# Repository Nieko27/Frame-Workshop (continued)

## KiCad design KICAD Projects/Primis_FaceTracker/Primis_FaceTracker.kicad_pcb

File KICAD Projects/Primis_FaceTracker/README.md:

### Status

| 🛑R&D | hw: EV2 | 
| -------- | ------- |

> This accessory is experimental. The latest hardware revision is either untested, incomplete, or broken. Capabilities are unproven. Form factor and design requirements may change entirely. Intended for use by hardware contributors.

### TODO
* Copper pads under power supply
* Clean up and condense
* ESD Protection
# Face Tracker (Headset-Agnostic Version)
Headset-agnostic face tracker. Can be used with Frame by using the USB-C port on the battery.
## Current Isseus
Q1 is setup improperly, removing it and R10 as well as bridging the now empty pads solves the issue. Will fix in EV3 along with some changes to layout and LEDs.

### Schematics

### PCB

### EV2

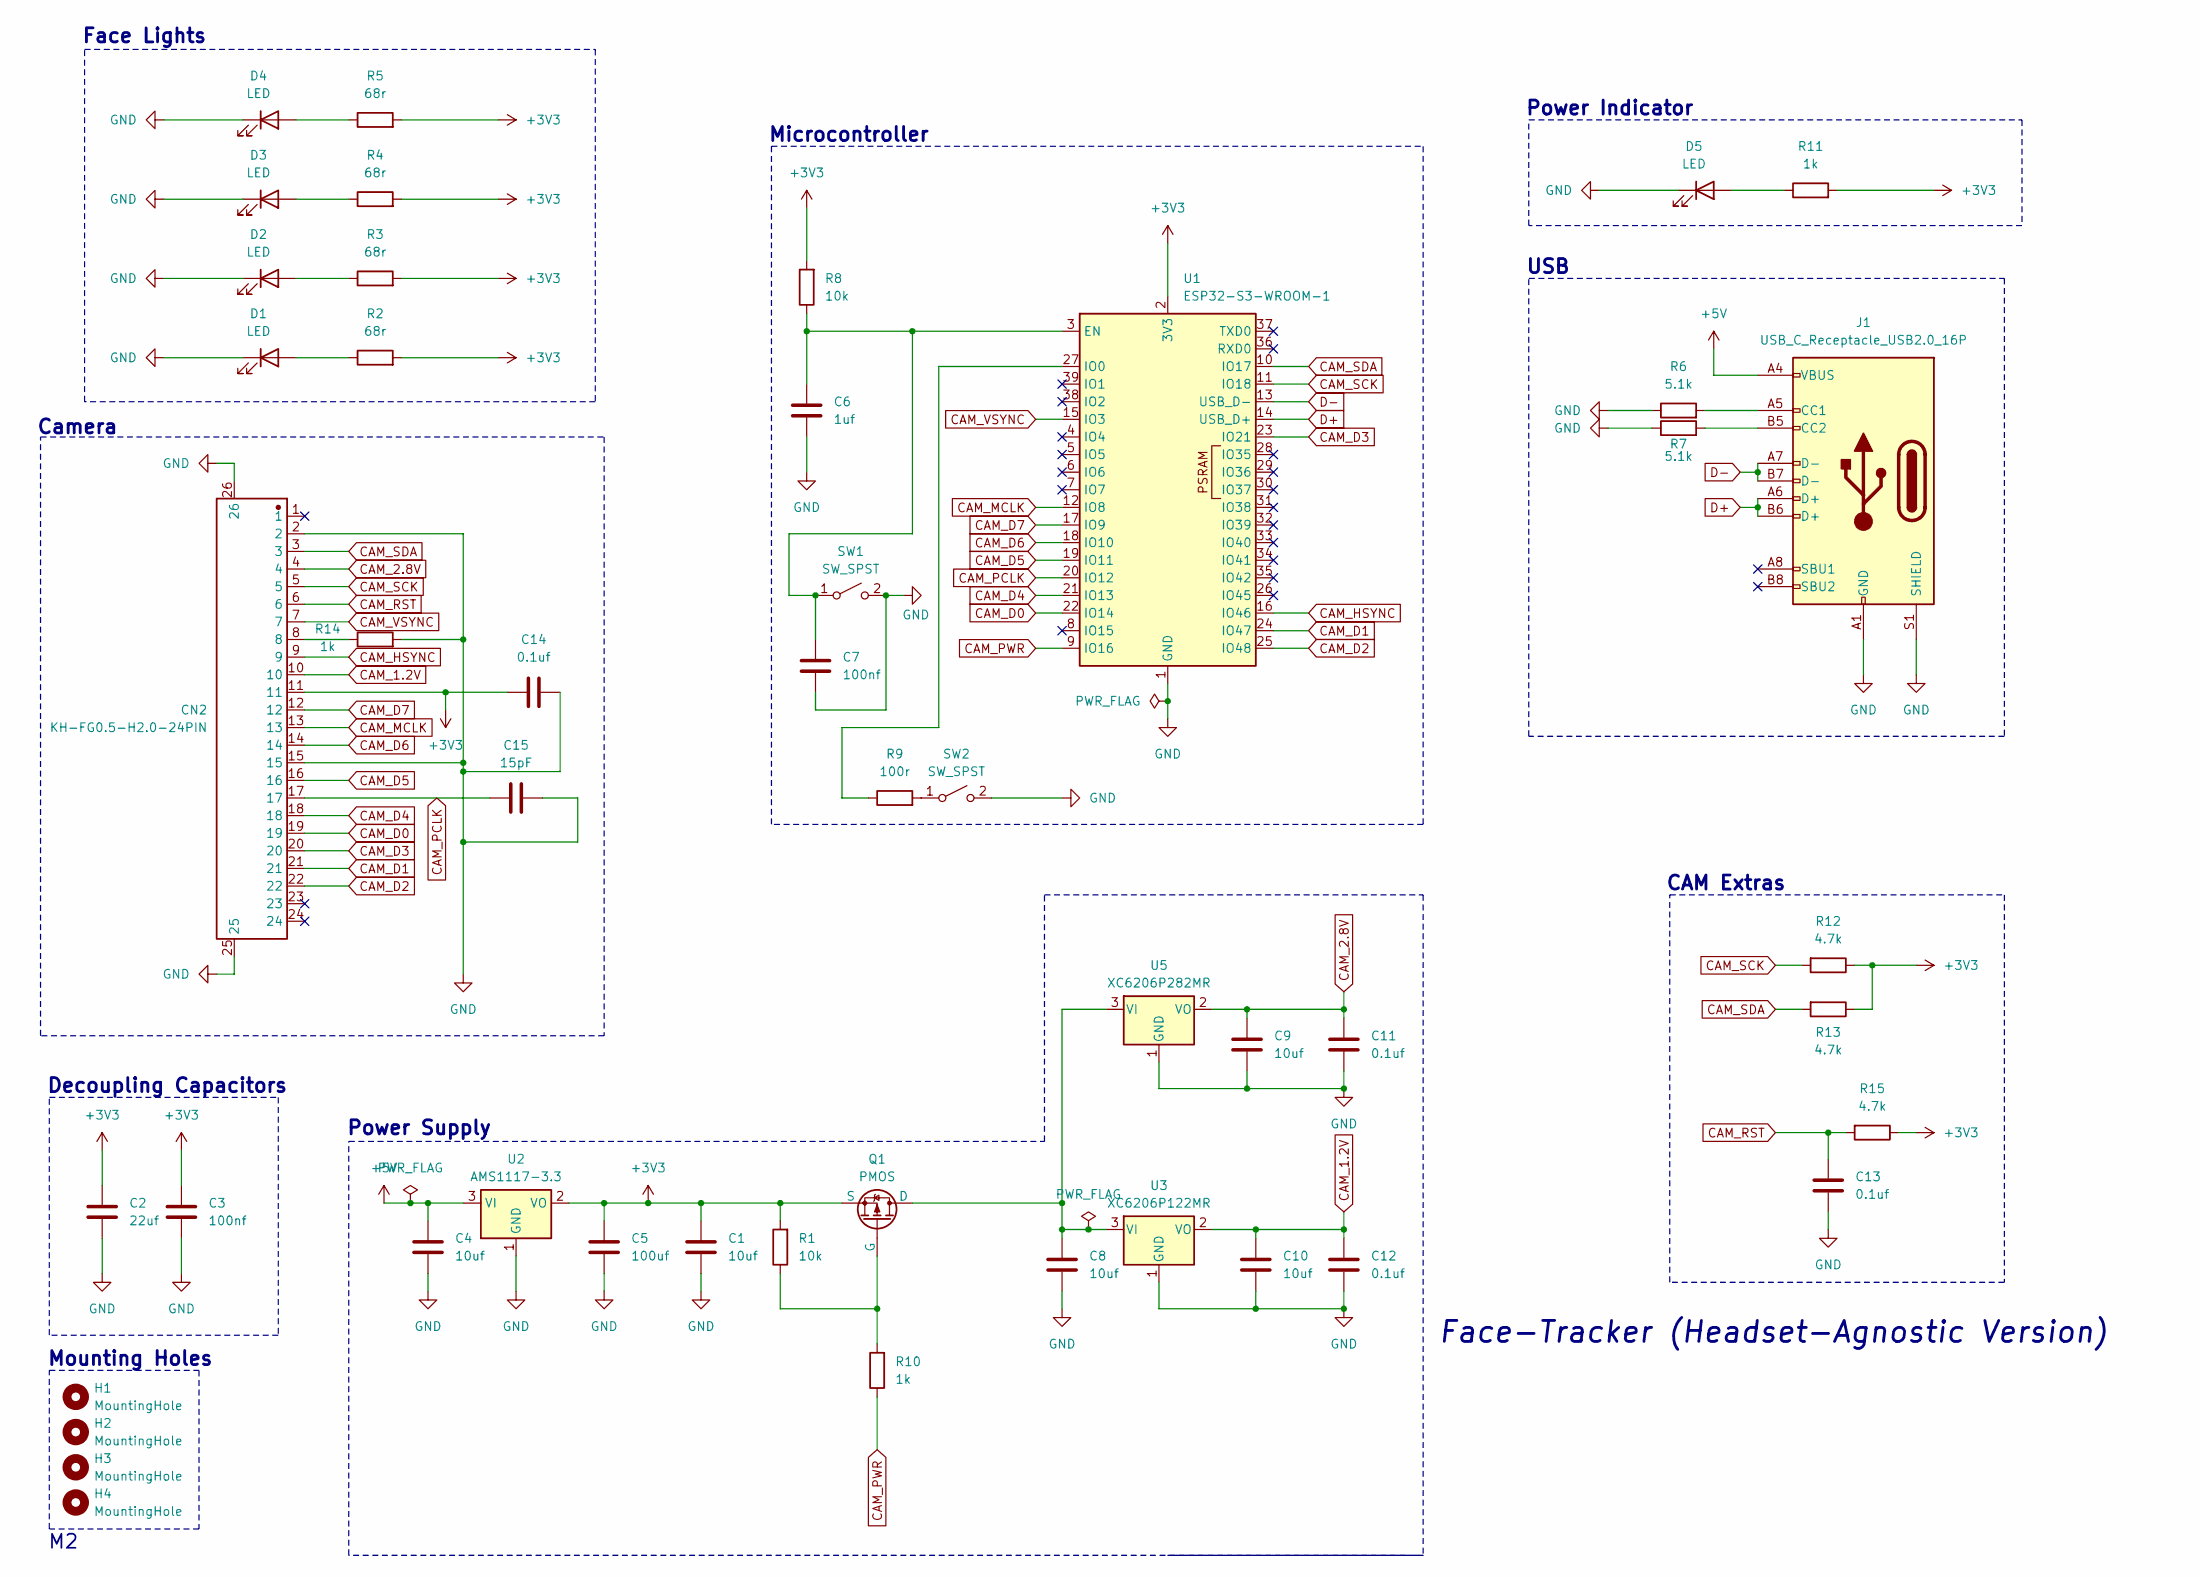
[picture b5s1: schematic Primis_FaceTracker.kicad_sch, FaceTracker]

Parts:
C1, C4, C8, C9, C10: 10uf; C_0805_2012Metric
C2: 22uf; C_0805_2012Metric
C3, C7: 100nf; C_0603_1608Metric
C5: 100uf; C_1206_3216Metric
C6: 1uf; C_0603_1608Metric
C11, C12, C13, C14: 0.1uf; C_0603_1608Metric
C15: 15pF; C_0603_1608Metric
CN2: KH-FG0.5-H2.0-24PIN; FPC-SMD_KH-FG0.5-H2.0-24PIN
D1, D2, D3, D4, D5: LED; LED_0805_2012Metric
H1, H2, H3, H4: MountingHole; MountingHole_2.2mm_M2
J1: USB_C_Receptacle_USB2.0_16P; USB_C_Receptacle_HRO_TYPE-C-31-M-12
Q1: PMOS; SOT-23
R1, R8: 10k; R_0805_2012Metric
R2, R3, R4, R5: 68r; R_0603_1608Metric
R6, R7: 5.1k; R_0805_2012Metric
R9: 100r; R_0603_1608Metric
R10, R11, R14: 1k; R_0805_2012Metric
R12, R13, R15: 4.7k; R_0805_2012Metric
SW1, SW2: SW_SPST; SW_SPST_TS-1088-xR020
U1: ESP32-S3-WROOM-1
U2: AMS1117-3.3; SOT-223-3_TabPin2
U3: XC6206P122MR; SOT-23-3
U5: XC6206P282MR; SOT-23-3

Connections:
+3V3: C1.1, C2.1, C3.1, C5.1, C14.1, CN2.11, Q1.3 (S), R1.2, R2.2, R3.2, R4.2, R5.2, R8.2, R11.2, R12.1, R13.1, R15.1, U1.2 (3V3), U2.2 (VO)
+5V: C4.1, J1.A4 (VBUS), J1.A9 (VBUS), J1.B4 (VBUS), J1.B9 (VBUS), U2.3 (VI)
CAM_1.2V: C10.1, C12.1, CN2.10, U3.2 (VO)
CAM_2.8V: C9.1, C11.1, CN2.4, U5.2 (VO)
CAM_D0: CN2.19, U1.22 (IO14)
CAM_D1: CN2.21, U1.24 (IO47)
CAM_D2: CN2.22, U1.25 (IO48)
CAM_D3: CN2.20, U1.23 (IO21)
CAM_D4: CN2.18, U1.21 (IO13)
CAM_D5: CN2.16, U1.19 (IO11)
CAM_D6: CN2.14, U1.18 (IO10)
CAM_D7: CN2.12, U1.17 (IO9)
CAM_HSYNC: CN2.9, U1.16 (IO46)
CAM_MCLK: CN2.13, U1.12 (IO8)
CAM_PCLK: C15.1, CN2.17, U1.20 (IO12)
CAM_PWR: R10.1, U1.9 (IO16)
CAM_RST: C13.1, CN2.6, R15.2
CAM_SCK: CN2.5, R12.2, U1.11 (IO18)
CAM_SDA: CN2.3, R13.2, U1.10 (IO17)
CAM_VSYNC: CN2.7, U1.15 (IO3)
D+: J1.A6 (D+), J1.B6 (D+), U1.14 (USB_D+)
D-: J1.A7 (D-), J1.B7 (D-), U1.13 (USB_D-)
GND: C1.2, C2.2, C3.2, C4.2, C5.2, C6.2, C7.1, C8.2, C9.2, C10.2, C11.2, C12.2, C13.2, C14.2, C15.2, CN2.2, CN2.15, CN2.25, CN2.26, D1.1 (K), D2.1 (K), D3.1 (K), D4.1 (K), D5.1 (K), J1.A1 (GND), J1.A12 (GND), J1.B1 (GND), J1.B12 (GND), J1.S1 (SHIELD), R6.1, R7.1, R14.2, SW1.2 (B), SW2.2 (B), U1.1 (GND), U1.40 (GND), U1.41 (GND), U2.1 (GND), U3.1 (GND), U5.1 (GND)
unnamed: CN2.8, R14.1
unnamed: D1.2 (A), R2.1
unnamed: D2.2 (A), R3.1
unnamed: D3.2 (A), R4.1
unnamed: D4.2 (A), R5.1
unnamed: D5.2 (A), R11.1
unnamed: J1.A5 (CC1), R6.2
unnamed: J1.B5 (CC2), R7.2
unnamed: C8.1, Q1.1 (D), U3.3 (VI), U5.3 (VI)
unnamed: Q1.2 (G), R1.1, R10.2
unnamed: C6.1, C7.2, R8.1, SW1.1 (A), U1.3 (EN)
unnamed: R9.2, SW2.1 (A)
unnamed: R9.1, U1.27 (IO0)

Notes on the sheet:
Decoupling Capacitors
Face Lights
Mounting Holes
Microcontroller
Power Indicator
Face-Tracker (Headset-Agnostic Version)
USB
Camera
CAM Extras
Power Supply

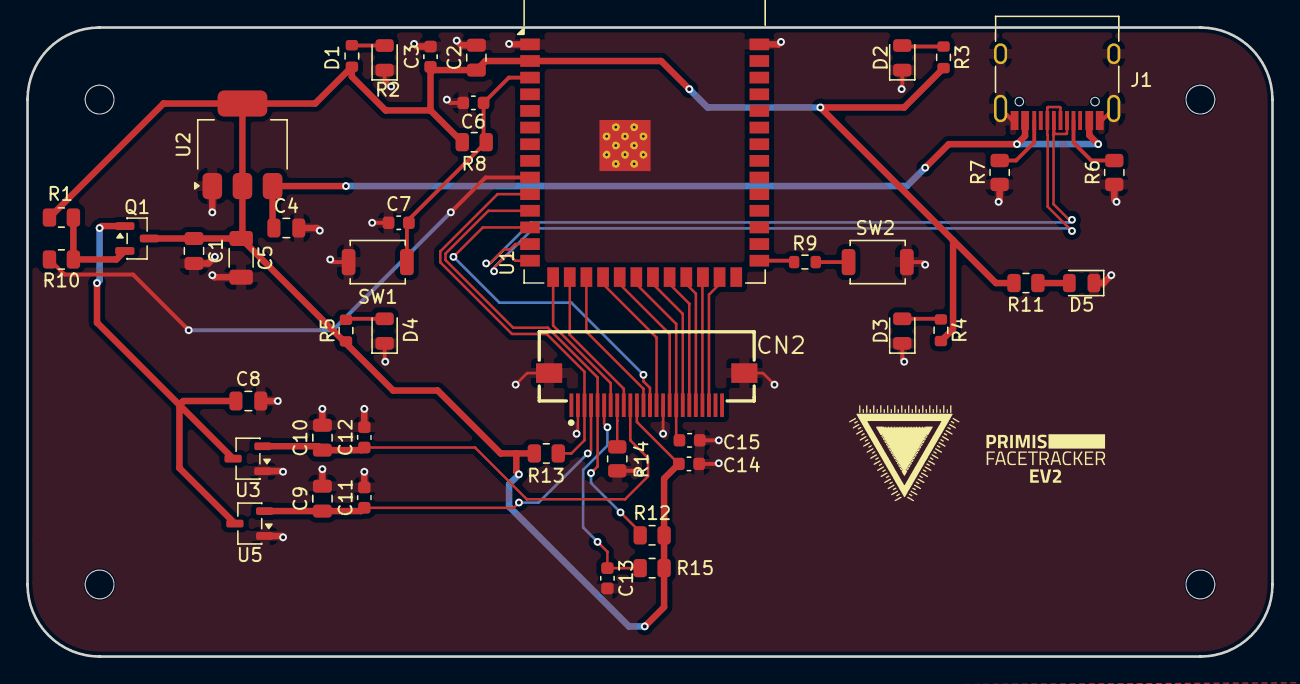
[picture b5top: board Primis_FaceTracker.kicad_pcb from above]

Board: 2 copper layers, 95.0 x 48.0 mm, 48 parts (0 on the bottom side), 36 nets.

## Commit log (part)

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2026-01-17 Clean
2026-01-17 Structure
2026-01-17 Structure2
2026-01-26 NameFix
2026-02-11 Face Tracker and Versipellis Clean
    -Organised the face tracker PCB a bit more
    -Added TODO to face tracker README
    -Organised Versipellis schematics
    -Updated images
2026-02-17 Gerbers plus clean up
    -Added gerbers for the face tracker and versipellis
    -Shrunk the face tracker and cleaned up
    -Fixed some DRC issues with both projects
2026-03-10 Quick Update
2026-04-26 FaceTracker fixes and Dongle rework
    -Fixed some mistakes on the Facetracker with the camera power lines.
    -Some part swaps and additions on the dongle to match the JLCPCBs catalogue
2026-04-27 Usb swap
    -Changed the dongle to another usb
2026-05-02 Dongle Cleanup
    -CLeanup before final
2026-05-02 Versipellis EV1 Final + General Github updates
    -Fixed a few remaining issues with Versipellis EV1
    -Created production files for Versipellis
    -Updated pictures for all projects
2026-05-13 Quick EV1 Dongle Fixes
    -Made some last minute fixes
2026-05-19 Organised + Added Turrim and Model
    -Added folder structure for all files types
    -Added general folder for small supplementary projects
    -Added Turrim (Dongle hub for Frame dongles)
    -Added PCB model for the Frame dongles
2026-05-26 Big Update
    -Added Versipellis pictures
    -Split Turrim into 2 versions, a simple, cheap 1 port version and a more complex 4 port hub version.
    -Started work on Locus
2026-05-26 Readme fix
2026-05-26 fix2
2026-06-25 VERSIPELLIS EV2 + TURRIM Production files
    -Swapped to a tag connect for programming VERSIPELLIS
    -Moved crystal closer to the NRF on VERSIPELLIS
    -Fixed swapped lines on usb on VERSIPELLIS
    -TURRIM cleanup and production files added
2026-06-29 VERSIPELLIS/TURRIM Model files
    -Added VERSIPELLIS EV2 model
    -Added TURRIM model
    -Added VERSIPELLIS case models
    -Update images
